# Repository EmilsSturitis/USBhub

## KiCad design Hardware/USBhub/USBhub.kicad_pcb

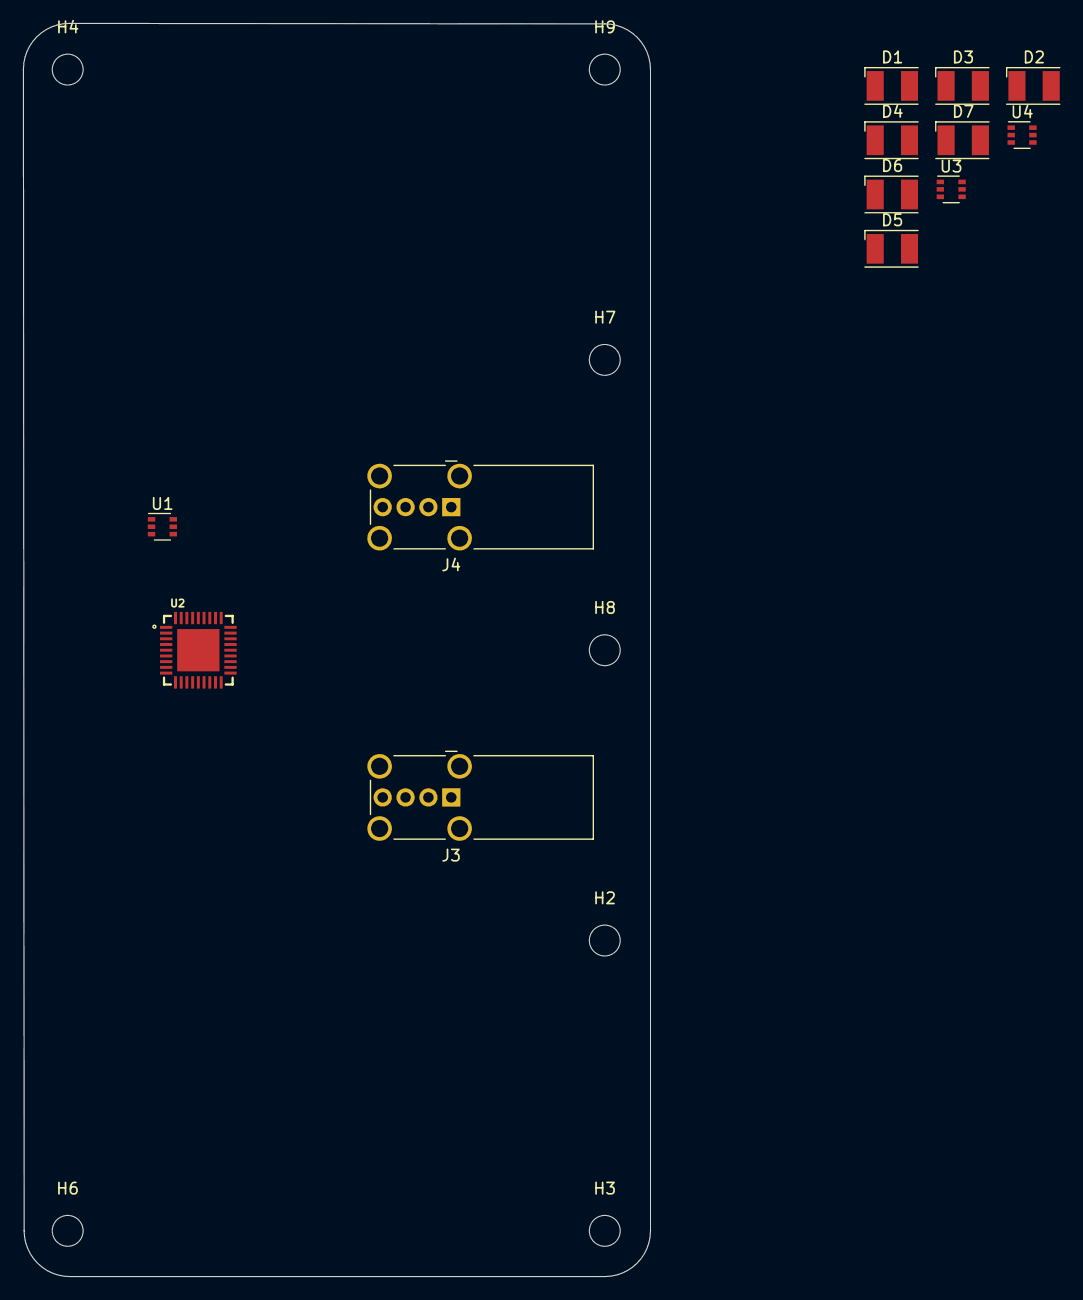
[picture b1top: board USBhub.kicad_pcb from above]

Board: 2 copper layers, 54.9 x 109.6 mm, 23 parts (0 on the bottom side), 4 nets, no tracks yet.

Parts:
D1, D2, D3, D4, D5, D6, D7: LED; LED_PLCC-2
H1, H2, H3, H4, H5, H6, H7, H8, H9, H10: MountingHole; MountingHole_2.7mm_M2.5
J3, J4: USB_A; USB_A_Wuerth_614004134726_Horizontal
U1, U3, U4: NUP4202; SOT-363_SC-70-6
U2: USB2512B-I/M2; QFN50P600X600X100-37N

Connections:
unnamed: U1.6, U2.30 (USBDM_UP)
unnamed: U1.4, U2.31 (USBDP_UP)
unnamed: U2.5 (VDDA33), U2.10 (VDDA33), U2.29 (VDDA33), U2.36 (VDDA33)
unnamed: U2.15 (VDD33), U2.23 (VDD33)

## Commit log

2023-01-20 some small updates
2023-02-12 small updates
2023-02-17 small updates, version to 7.0
